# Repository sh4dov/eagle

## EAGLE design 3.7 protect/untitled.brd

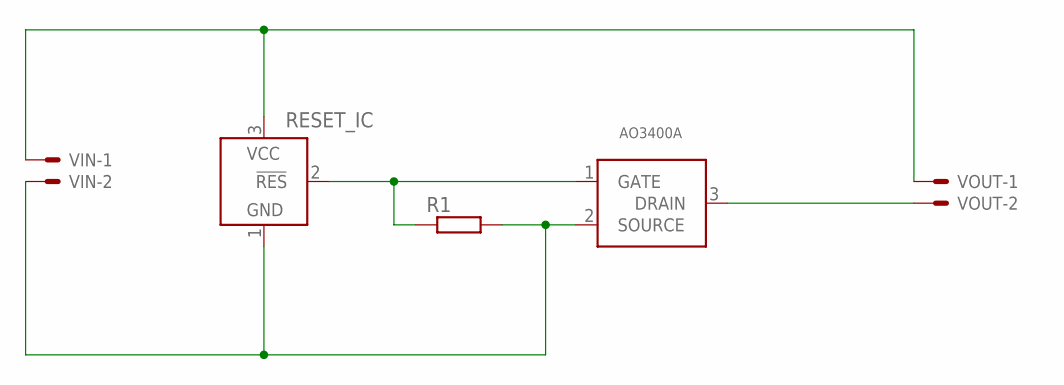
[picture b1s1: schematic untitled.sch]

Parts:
MOSFET: AO3400A; SOT-23
R1: R-EU_R1206; R1206
RESET_IC: TCM809; SOT23B-3
VIN: 22-23-2021
VOUT: 22-23-2021

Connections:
GND: MOSFET.2 (SOURCE), R1.2, RESET_IC.1 (GND), VIN.2
unnamed: MOSFET.3 (DRAIN), VOUT.2
unnamed: MOSFET.1 (GATE), R1.1, RESET_IC.2 (!RES)
VCC: RESET_IC.3 (VCC), VIN.1, VOUT.1

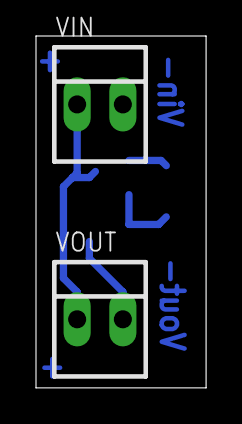
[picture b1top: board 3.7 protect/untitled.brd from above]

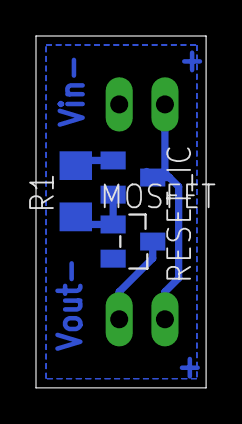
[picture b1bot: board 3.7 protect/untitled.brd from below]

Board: 2 copper layers, 9.4 x 19.5 mm, 5 parts (3 on the bottom side), 4 nets.

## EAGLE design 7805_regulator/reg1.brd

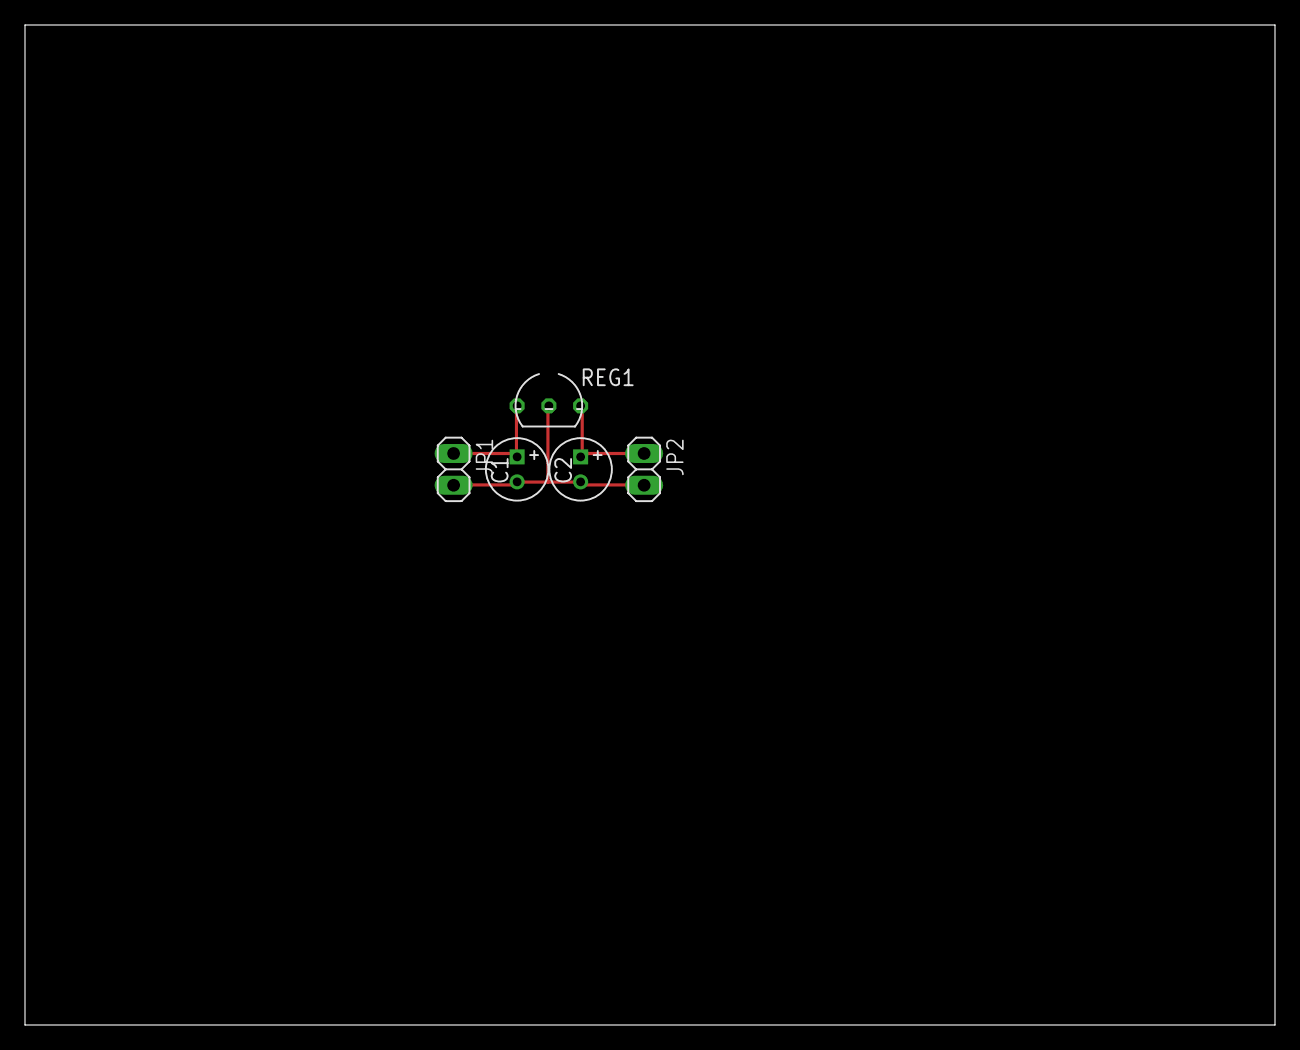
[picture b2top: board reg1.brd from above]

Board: 2 copper layers, 100.0 x 80.0 mm, 5 parts (0 on the bottom side), 3 nets.

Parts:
C1, C2: 100uF; 050_020
JP1, JP2: 1X02
REG1: 7805; TO92-

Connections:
+5V: C2.+, JP2.1, REG1.3
+9V: C1.+, JP1.1, REG1.1
GND: C1.-, C2.-, JP1.2, JP2.2, REG1.2

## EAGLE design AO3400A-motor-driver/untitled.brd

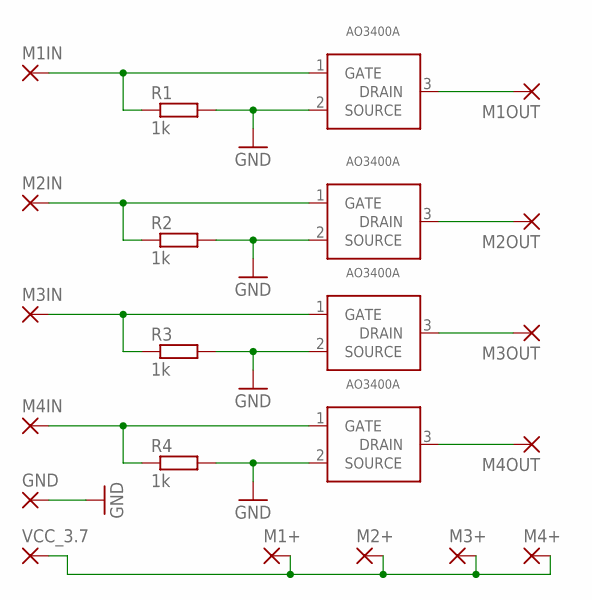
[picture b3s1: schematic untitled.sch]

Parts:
GND: SMD2; SMD1,27-2,54
M1+, M1IN, M1OUT, M2+, M2IN, M2OUT, M3+, M3IN, M3OUT, M4+, M4IN, M4OUT: SMD2; SMD1,27-2,54
R1, R2, R3, R4: 1k; R1206
U$1, U$2, U$3, U$4: AO3400A; SOT-23
VCC_3.7: SMD2; SMD1,27-2,54

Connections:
GND: GND.1, R1.2, R2.2, R3.2, R4.2, U$1.2 (SOURCE), U$2.2 (SOURCE), U$3.2 (SOURCE), U$4.2 (SOURCE)
M1OUT: M1OUT.1, U$1.3 (DRAIN)
unnamed: M1IN.1, R1.1, U$1.1 (GATE)
unnamed: M4IN.1, R4.1, U$4.1 (GATE)
unnamed: M2IN.1, R2.1, U$2.1 (GATE)
unnamed: M3IN.1, R3.1, U$3.1 (GATE)
unnamed: M1+.1, M2+.1, M3+.1, M4+.1, VCC_3.7.1
unnamed: M2OUT.1, U$2.3 (DRAIN)
unnamed: M3OUT.1, U$3.3 (DRAIN)
unnamed: M4OUT.1, U$4.3 (DRAIN)

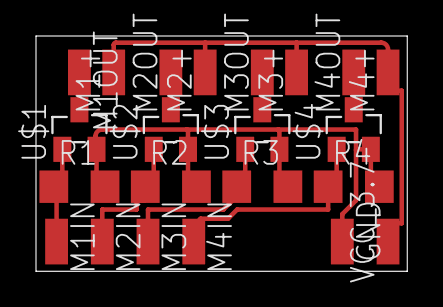
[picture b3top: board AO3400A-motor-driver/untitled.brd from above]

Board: 2 copper layers, 20.6 x 13.1 mm, 22 parts (0 on the bottom side), 10 nets.

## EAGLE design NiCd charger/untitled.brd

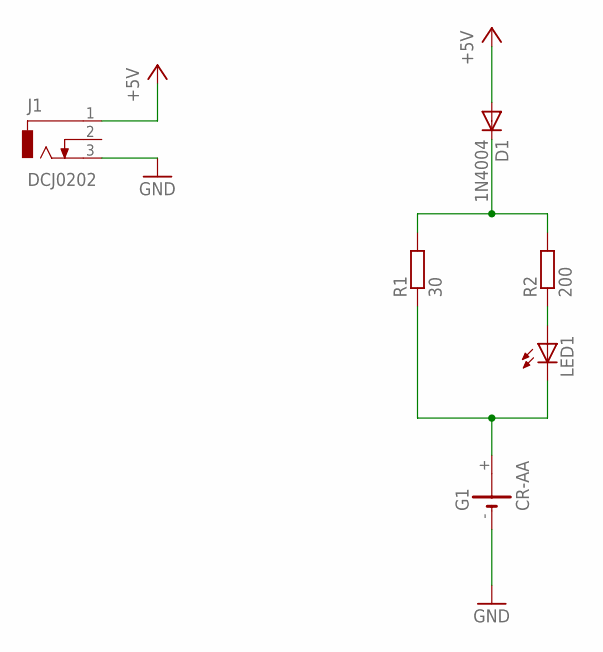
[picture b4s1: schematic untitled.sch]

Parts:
D1: 1N4004; DO41-10
G1: CR-AA; CRAA
J1: DCJ0202
LED1: LEDCHIP-LED0805; CHIP-LED0805
R1: 30; M1206
R2: 200; M1206

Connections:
+5V: D1.A, J1.1
GND: G1.-, J1.3
unnamed: D1.C, R1.2, R2.2
unnamed: LED1.A, R2.1
unnamed: G1.+, LED1.C, R1.1

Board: 2 copper layers, 6 parts (0 on the bottom side), 5 nets, no tracks yet.

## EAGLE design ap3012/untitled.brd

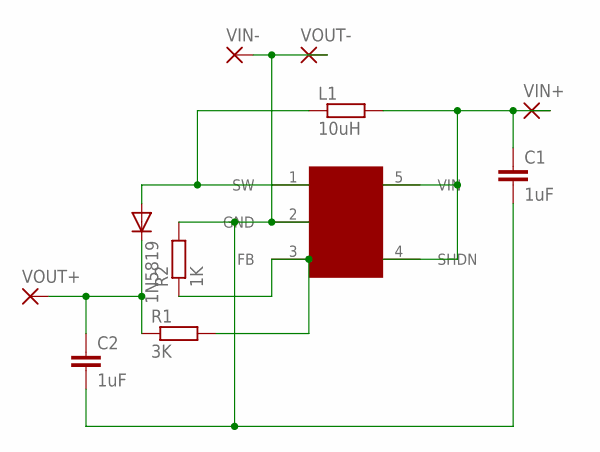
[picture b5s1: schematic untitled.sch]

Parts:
1N5819: DIODE-DO214AC; DO214AC
C1, C2: 1uF; C1206
L1: 10uH; R0805
R1: 3K; R1206
R2: 1K; R1206
U$8: AP3012; SOT-23-5
VIN+: SMD2; SMD1,27-2,54
VIN-: SMD2; SMD1,27-2,54
VOUT+: SMD2; SMD1,27-2,54
VOUT-: SMD2; SMD1,27-2,54

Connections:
unnamed: 1N5819.A, L1.1, U$8.1 (SW)
unnamed: C1.1, L1.2, U$8.4 (SHDN), U$8.5 (VIN), VIN+.1
unnamed: 1N5819.C, C2.1, R1.1, VOUT+.1
unnamed: R1.2, R2.1, U$8.3 (FB)
unnamed: C1.2, C2.2, R2.2, U$8.2 (GND), VIN-.1, VOUT-.1

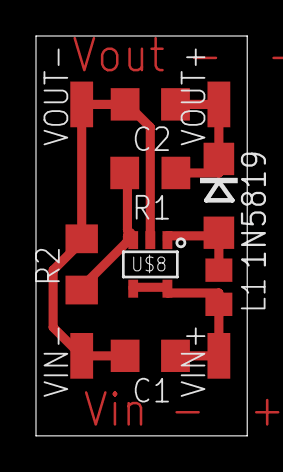
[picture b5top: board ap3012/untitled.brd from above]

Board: 2 copper layers, 11.7 x 22.2 mm, 11 parts (0 on the bottom side), 5 nets.
